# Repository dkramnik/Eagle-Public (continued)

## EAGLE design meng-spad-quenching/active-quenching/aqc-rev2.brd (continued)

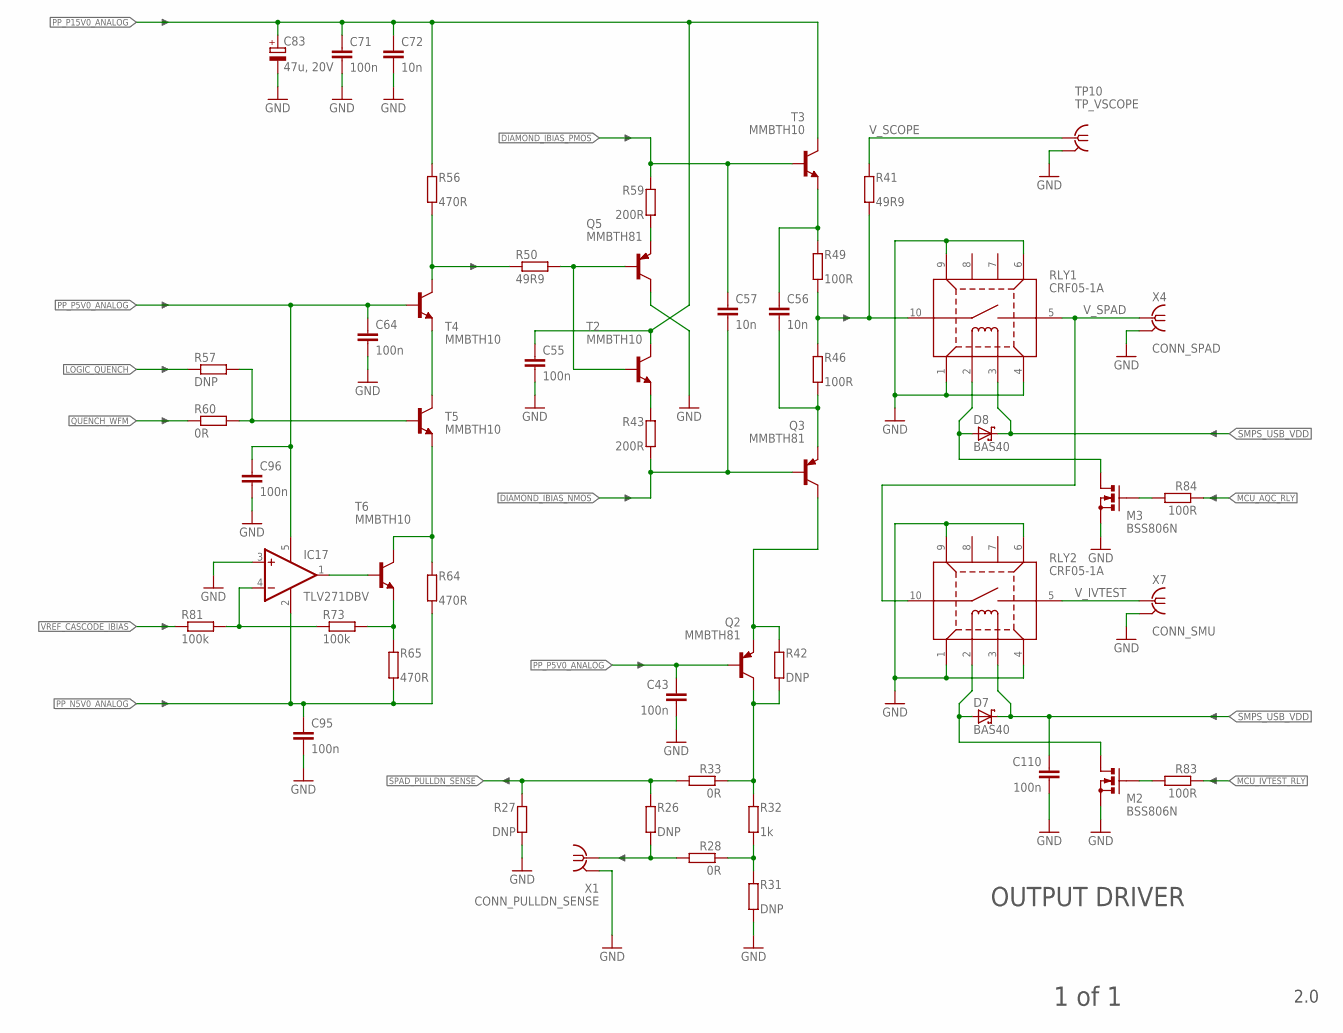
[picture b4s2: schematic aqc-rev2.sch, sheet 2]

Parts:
C43, C55, C64, C71, C95, C96, C110: 100n; C0603
C56, C57, C72: 10n; C0603
C83: 47u, 20V; CT7343
D7, D8: BAS40; SOT23
IC17: TLV271DBV; SOT23-5
M2, M3: BSS806N; SOT23R_INFINEON
Q2, Q3, Q5: MMBTH81; SOT23-BEC
R26, R27, R31, R42, R57: DNP; R0603
R28, R33, R60: 0R; R0603
R32: 1k; R0603
R41, R50: 49R9; R0603
R43, R59: 200R; R0603
R46, R49, R83, R84: 100R; R0603
R56, R64, R65: 470R; R0603
R73, R81: 100k; R0603
RLY1, RLY2: CRF05-1A; MEDER_RELAY_CRF
T2, T3, T4, T5, T6: MMBTH10; SOT23-BEC
TP10: TP_VSCOPE; JOHNSON-129-0701-30X
X1: CONN_PULLDN_SENSE; J502-ND-142-0711-871/876; MPN 142-0711-871
X4: CONN_SPAD; J502-ND-142-0711-871/876
X7: CONN_SMU; J502-ND-142-0711-871/876

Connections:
CASC_BIAS_B: IC17.1 (OUT), T6.B
CASC_BIAS_C: R64.2, T5.E, T6.C
CASC_BIAS_E: R65.2, R73.1, T6.E
CASC_BIAS_VGND: IC17.4 (-IN), R73.2, R81.1
CASC_MIDPT: T4.E, T5.C
DIAMOND_IBIAS_NMOS: C57.2, Q3.B, R43.1; also elsewhere on the board
DIAMOND_IBIAS_PMOS: C57.1, R59.2, T3.B; also elsewhere on the board
GND: C43.2, C55.2, C64.2, C71.2, C72.2, C83.-, C95.2, C96.2, C110.2, IC17.3 (+IN), M2.2 (S), M3.2 (S), Q5.C, R27.1, R31.1, RLY1.1 (PIN1), RLY1.4 (PIN4), RLY1.6 (PIN6), RLY1.9 (PIN9), RLY2.1 (PIN1), RLY2.4 (PIN4), RLY2.6 (PIN6), RLY2.9 (PIN9), TP10.GND1 (GND), TP10.GND2 (GND), X1.G@1 (GND), X1.G@2 (GND), X1.G@3 (GND), X1.G@4 (GND), X4.G@1 (GND), X4.G@2 (GND), X4.G@3 (GND), X4.G@4 (GND), X7.G@1 (GND), X7.G@2 (GND), X7.G@3 (GND), X7.G@4 (GND); also elsewhere on the board
LOGIC_QUENCH: R57.2; also elsewhere on the board
MCU_AQC_RLY: R84.2; also elsewhere on the board
MCU_IVTEST_RLY: R83.2; also elsewhere on the board
unnamed: R57.1, R60.1, T5.B
unnamed: M3.1 (G), R84.1
unnamed: D8.1 (A), M3.3 (D), RLY1.2 (PIN2)
unnamed: C56.1, R49.2, T3.E
unnamed: D7.1 (A), M2.3 (D), RLY2.2 (PIN2)
unnamed: Q2.E, Q3.C, R42.2
unnamed: Q5.E, R59.1
unnamed: R43.2, T2.E
unnamed: C56.2, Q3.E, R46.1
unnamed: M2.1 (G), R83.1
unnamed: Q5.B, R50.1, T2.B
unnamed: R50.2, R56.1, T4.C
unnamed: R41.1, R46.2, R49.1, RLY1.10 (PIN10)
unnamed: Q2.C, R32.2, R33.2, R42.1
unnamed: R28.2, R31.2, R32.1
unnamed: R26.1, R28.1, X1.1
PP_N5V0_ANALOG: C95.1, IC17.2 (V-), R64.1, R65.1; also elsewhere on the board
PP_P5V0_ANALOG: C43.1, C64.1, C96.1, IC17.5 (V+), Q2.B, T4.B; also elsewhere on the board
PP_P15V0_ANALOG: C55.1, C71.1, C72.1, C83.+, R56.2, T2.C, T3.C; also elsewhere on the board
QUENCH_WFM: R60.2; also elsewhere on the board
SMPS_USB_VDD: C110.1, D7.3 (C), D8.3 (C), RLY1.3 (PIN3), RLY2.3 (PIN3); also elsewhere on the board
SPAD_PULLDN_SENSE: R26.2, R27.2, R33.1; also elsewhere on the board
VREF_CASCODE_IBIAS: R81.2; also elsewhere on the board
V_IVTEST: RLY2.5 (PIN5), X7.1
V_SCOPE: R41.2, TP10.SIG (1)
V_SPAD: RLY1.5 (PIN5), RLY2.10 (PIN10), X4.1

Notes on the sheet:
OUTPUT DRIVER
2.0
1 of 1

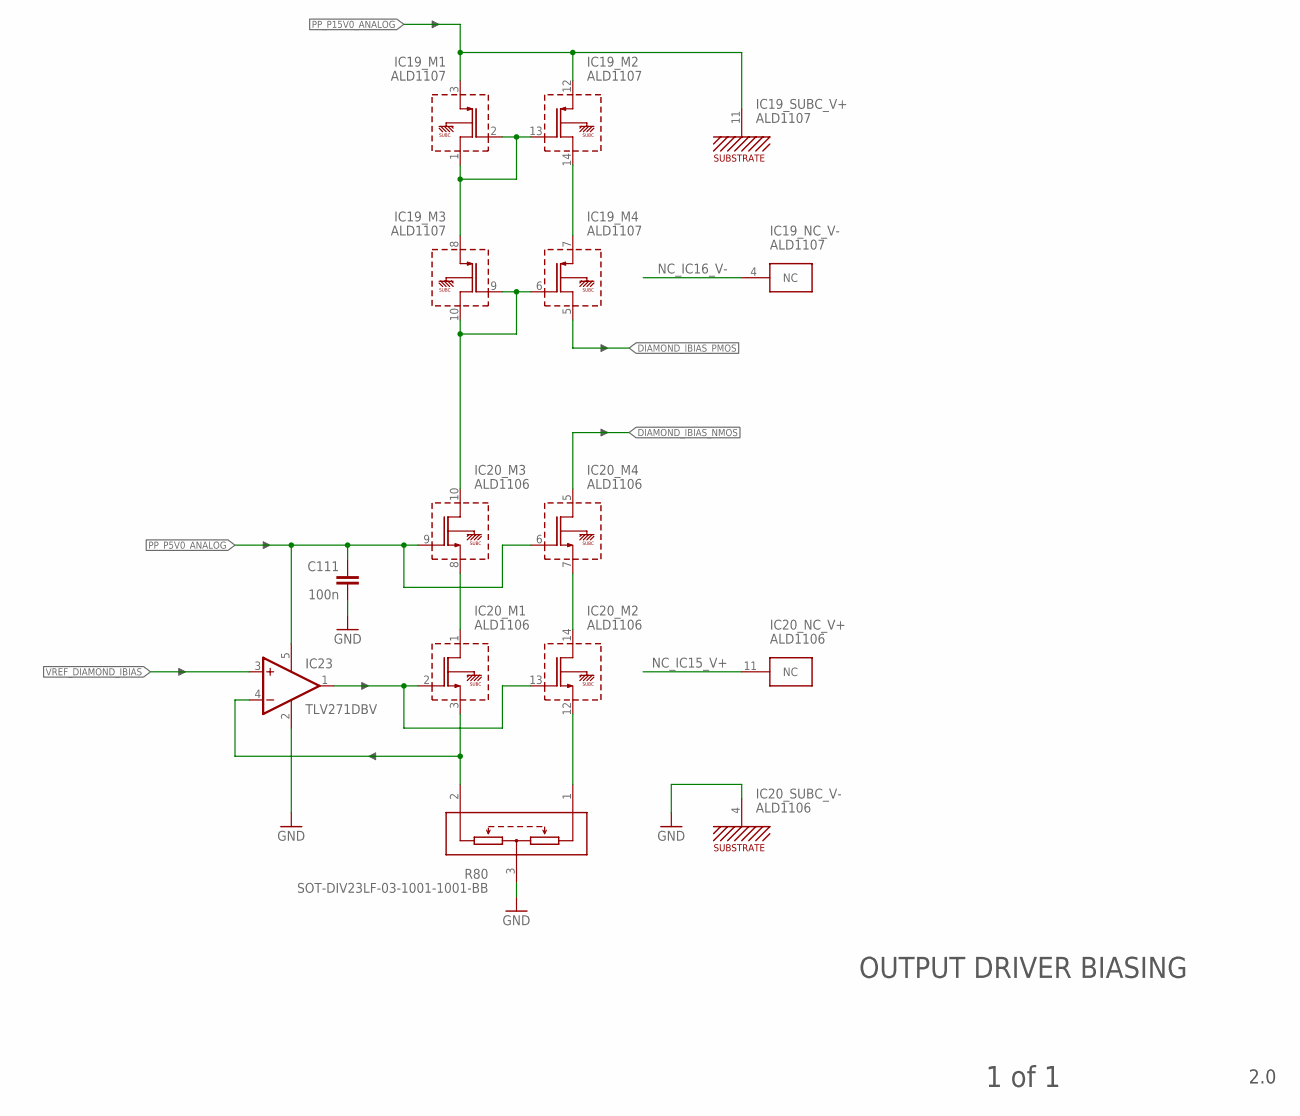
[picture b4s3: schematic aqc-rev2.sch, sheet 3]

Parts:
C111: 100n; C0603
IC19: ALD1107; SO14
IC20: ALD1106; SO14
IC23: TLV271DBV; SOT23-5
R80: SOT-DIV23LF-03-1001-1001-BB; SOT23C

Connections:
DIAMOND_IBIAS_NMOS: IC20.5 (D); also elsewhere on the board
DIAMOND_IBIAS_PMOS: IC19.5 (D); also elsewhere on the board
GND: C111.2, IC20.4 (SUBC), IC23.2 (V-), R80.3 (MIDDLE); also elsewhere on the board
unnamed: IC20.1 (D), IC20.8 (S)
unnamed: IC20.7 (S), IC20.14 (D)
unnamed: IC20.3 (S), IC23.4 (-IN), R80.2 (TOP)
unnamed: IC20.2 (G), IC20.13 (G), IC23.1 (OUT)
unnamed: IC20.12 (S), R80.1 (BOTTOM)
unnamed: IC19.1 (D), IC19.2 (G), IC19.8 (S), IC19.13 (G)
unnamed: IC19.7 (S), IC19.14 (D)
unnamed: IC19.6 (G), IC19.9 (G), IC19.10 (D), IC20.10 (D)
NC_IC15_V+: IC20.11 (NC)
NC_IC16_V-: IC19.4 (NC)
PP_P5V0_ANALOG: C111.1, IC20.6 (G), IC20.9 (G), IC23.5 (V+); also elsewhere on the board
PP_P15V0_ANALOG: IC19.3 (S), IC19.11 (SUBC), IC19.12 (S); also elsewhere on the board
VREF_DIAMOND_IBIAS: IC23.3 (+IN); also elsewhere on the board

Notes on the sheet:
OUTPUT DRIVER BIASING
2.0
1 of 1

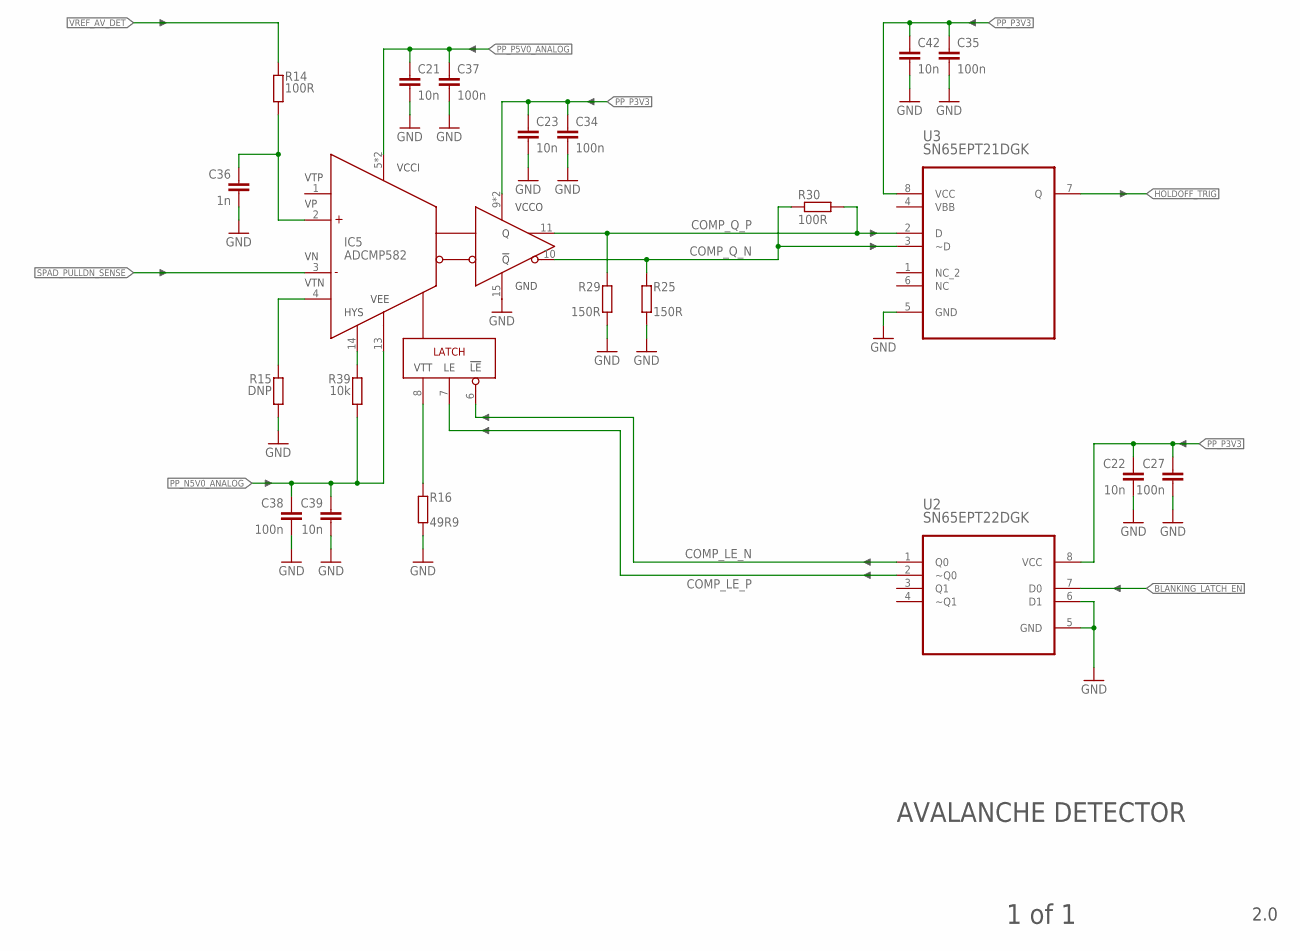
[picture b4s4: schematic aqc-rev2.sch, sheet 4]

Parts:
C21, C22, C23, C39, C42: 10n; C0402
C27, C34, C35, C37, C38: 100n; C0402
C36: 1n; C0603
IC5: ADCMP582; QFN50P300X300X80-16N
R14: 100R; R0603
R15: DNP; R0603
R16: 49R9; R0603
R25, R29: 150R; R0402
R30: 100R; R0402
R39: 10k; R0603
U2: SN65EPT22DGK; SOP65P490X110-8N
U3: SN65EPT21DGK; SOP65P490X110-8N

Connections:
BLANKING_LATCH_EN: U2.7 (D0); also elsewhere on the board
COMP_HYS: IC5.14 (HYS), R39.2
COMP_LE_N: IC5.6 (!LE), U2.1 (Q0)
COMP_LE_P: IC5.7 (LE), U2.2 (~Q0)
COMP_Q_N: IC5.10 (!Q), R25.1, R30.1, U3.3 (~D)
COMP_Q_P: IC5.11 (Q), R29.1, R30.2, U3.2 (D)
COMP_VP: C36.1, IC5.2 (VP), R14.1
COMP_VTN: IC5.4 (VTN), R15.2
COMP_VTT: IC5.8 (VTT), R16.1
GND: C21.2, C22.2, C23.2, C27.2, C34.2, C35.2, C36.2, C37.2, C38.2, C39.2, C42.2, IC5.15 (GND), R15.1, R16.2, R25.2, R29.2, U2.5 (GND), U2.6 (D1), U3.5 (GND); also elsewhere on the board
HOLDOFF_TRIG: U3.7 (Q); also elsewhere on the board
PP_N5V0_ANALOG: C38.1, C39.1, IC5.13 (VEE), R39.1; also elsewhere on the board
PP_P3V3: C22.1, C23.1, C27.1, C34.1, C35.1, C42.1, IC5.9 (VCCO), IC5.12 (VCCO), U2.8 (VCC), U3.8 (VCC); also elsewhere on the board
PP_P5V0_ANALOG: C21.1, C37.1, IC5.5 (VCCI), IC5.16 (VCCI); also elsewhere on the board
SPAD_PULLDN_SENSE: IC5.3 (VN); also elsewhere on the board
VBB: U3.4 (VBB)
VREF_AV_DET: R14.2; also elsewhere on the board

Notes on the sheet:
AVALANCHE DETECTOR
2.0
1 of 1

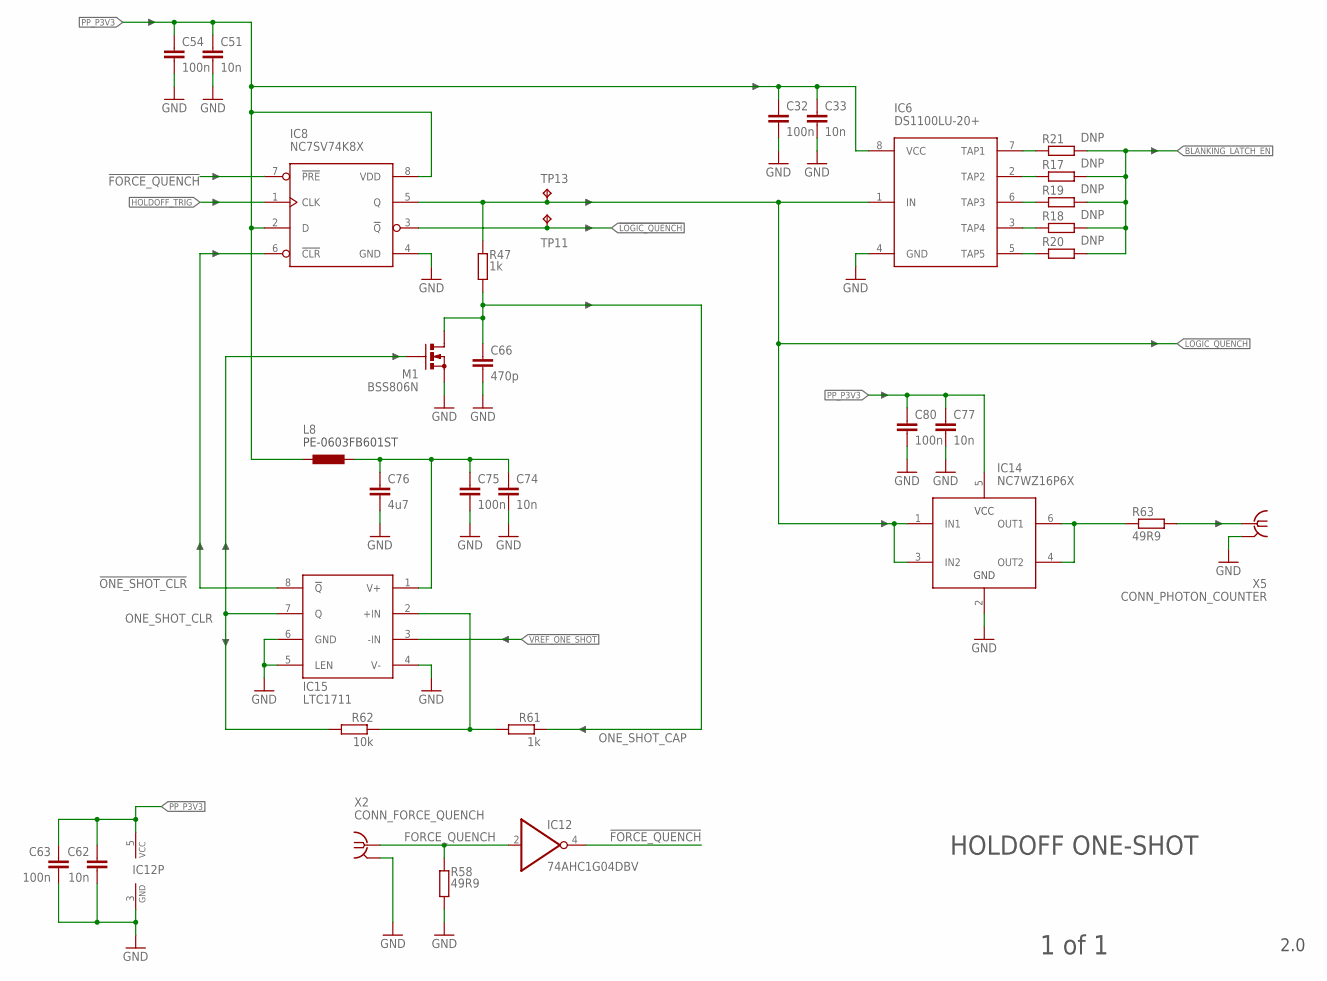
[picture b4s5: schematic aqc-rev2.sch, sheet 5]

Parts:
C32, C54, C63, C75, C80: 100n; C0402
C33, C51, C62, C74, C77: 10n; C0402
C66: 470p; C0603
C76: 4u7; C0603
IC6: DS1100LU-20+; MSOP8
IC8: NC7SV74K8X; US8_3.1MM_JDEC_MO-187
IC12: 74AHC1G04DBV; SOT23-5
IC14: NC7WZ16P6X; SC70-6L
IC15: LTC1711; MSOP8
L8: PE-0603FB601ST; R0603
M1: BSS806N; SOT23R_INFINEON
R17, R18, R19, R20, R21: DNP; R0603
R47, R61: 1k; R0603
R58, R63: 49R9; R0603
R62: 10k; R0603
TP11, TP13: TPTP06R; TP06R
X2: CONN_FORCE_QUENCH; J502-ND-142-0711-871/876; MPN 142-0711-871
X5: CONN_PHOTON_COUNTER; J502-ND-142-0711-871/876

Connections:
!FORCE_QUENCH: IC8.7 (!PRE), IC12.4 (O)
!LOGIC_QUENCH: IC8.3 (!Q), TP11.TP; also elsewhere on the board
!ONE_SHOT_CLR: IC8.6 (!CLR), IC15.8 (!Q)
BLANKING_LATCH_EN: R17.1, R18.1, R19.1, R20.1, R21.1; also elsewhere on the board
FORCE_QUENCH: IC12.2 (I), R58.2, X2.1
GND: C32.2, C33.2, C51.2, C54.2, C62.2, C63.2, C66.2, C74.2, C75.2, C76.2, C77.2, C80.2, IC6.4 (GND), IC8.4 (GND), IC12.3 (GND), IC14.2 (GND), IC15.4 (V-), IC15.5 (LEN), IC15.6 (GND), M1.2 (S), R58.1, X2.G@1 (GND), X2.G@2 (GND), X2.G@3 (GND), X2.G@4 (GND), X5.G@1 (GND), X5.G@2 (GND), X5.G@3 (GND), X5.G@4 (GND); also elsewhere on the board
HOLDOFF_TRIG: IC8.1 (CLK); also elsewhere on the board
LOGIC_QUENCH: IC6.1 (IN), IC8.5 (Q), IC14.1 (IN1), IC14.3 (IN2), R47.2, TP13.TP; also elsewhere on the board
unnamed: IC15.2 (+IN), R61.1, R62.2
unnamed: IC14.4 (OUT2), IC14.6 (OUT1), R63.2
ONE_SHOT_CAP: C66.1, M1.3 (D), R47.1, R61.2
ONE_SHOT_CLR: IC15.7 (Q), M1.1 (G), R62.1
PHOTON_COUNT_OUT: R63.1, X5.1
PP_P3V3: C32.1, C33.1, C51.1, C54.1, C62.1, C63.1, C77.1, C80.1, IC6.8 (VCC), IC8.2 (D), IC8.8 (VDD), IC12.5 (VCC), IC14.5 (VCC), L8.1; also elsewhere on the board
PP_P3V3_COMP: C74.1, C75.1, C76.1, IC15.1 (V+), L8.2
TAP1: IC6.7 (TAP1), R21.2
TAP2: IC6.2 (TAP2), R17.2
TAP3: IC6.6 (TAP3), R19.2
TAP4: IC6.3 (TAP4), R18.2
TAP5: IC6.5 (TAP5), R20.2
VREF_ONE_SHOT: IC15.3 (-IN); also elsewhere on the board

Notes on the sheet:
HOLDOFF ONE-SHOT
2.0
1 of 1

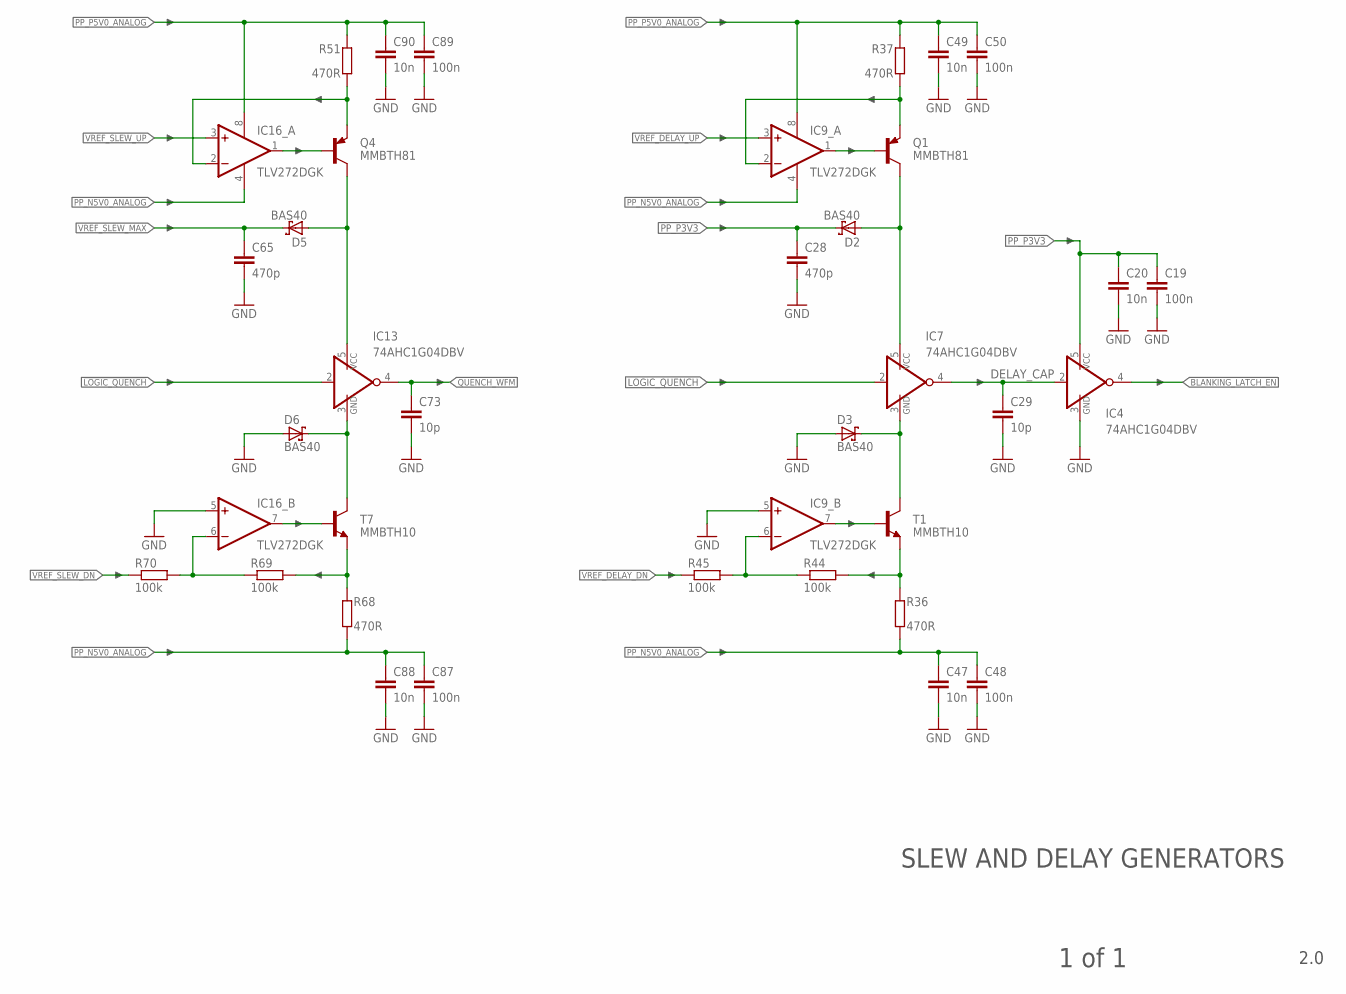
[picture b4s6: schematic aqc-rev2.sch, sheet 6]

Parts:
C19, C48, C50, C87, C89: 100n; C0402
C20, C47, C49, C88, C90: 10n; C0402
C28, C65: 470p; C0603
C29, C73: 10p; C0603
D2, D3, D5, D6: BAS40; SOT23
IC4, IC7, IC13: 74AHC1G04DBV; SOT23-5
IC9, IC16: TLV272DGK; MSOP8
Q1, Q4: MMBTH81; SOT23-BEC
R36, R37, R51, R68: 470R; R0603
R44, R45, R69, R70: 100k; R0603
T1, T7: MMBTH10; SOT23-BEC

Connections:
!LOGIC_QUENCH: IC13.2 (I); also elsewhere on the board
BLANKING_LATCH_EN: IC4.4 (O); also elsewhere on the board
DELAY_CAP: C29.1, IC4.2 (I), IC7.4 (O)
GND: C19.2, C20.2, C28.2, C29.2, C47.2, C48.2, C49.2, C50.2, C65.2, C73.2, C87.2, C88.2, C89.2, C90.2, D3.1 (A), D6.1 (A), IC4.3 (GND), IC9.5 (+IN), IC16.5 (+IN); also elsewhere on the board
LOGIC_QUENCH: IC7.2 (I); also elsewhere on the board
unnamed: IC16.2 (-IN), Q4.E, R51.1
unnamed: D5.1 (A), IC13.5 (VCC), Q4.C
unnamed: D6.3 (C), IC13.3 (GND), T7.C
unnamed: IC16.1 (OUT), Q4.B
unnamed: IC16.7 (OUT), T7.B
unnamed: IC16.6 (-IN), R69.2, R70.1
unnamed: D2.1 (A), IC7.5 (VCC), Q1.C
unnamed: D3.3 (C), IC7.3 (GND), T1.C
unnamed: IC9.7 (OUT), T1.B
unnamed: IC9.6 (-IN), R44.2, R45.1
unnamed: IC9.2 (-IN), Q1.E, R37.1
unnamed: IC9.1 (OUT), Q1.B
unnamed: R68.2, R69.1, T7.E
unnamed: R36.2, R44.1, T1.E
PP_N5V0_ANALOG: C47.1, C48.1, C87.1, C88.1, IC9.4 (V-), IC16.4 (V-), R36.1, R68.1; also elsewhere on the board
PP_P3V3: C19.1, C20.1, C28.1, D2.3 (C), IC4.5 (VCC); also elsewhere on the board
PP_P5V0_ANALOG: C49.1, C50.1, C89.1, C90.1, IC9.8 (V+), IC16.8 (V+), R37.2, R51.2; also elsewhere on the board
QUENCH_WFM: C73.1, IC13.4 (O); also elsewhere on the board
VREF_DELAY_DN: R45.2; also elsewhere on the board
VREF_DELAY_UP: IC9.3 (+IN); also elsewhere on the board
VREF_SLEW_DN: R70.2; also elsewhere on the board
VREF_SLEW_MAX: C65.1, D5.3 (C); also elsewhere on the board
VREF_SLEW_UP: IC16.3 (+IN); also elsewhere on the board

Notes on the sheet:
SLEW AND DELAY GENERATORS
2.0
1 of 1

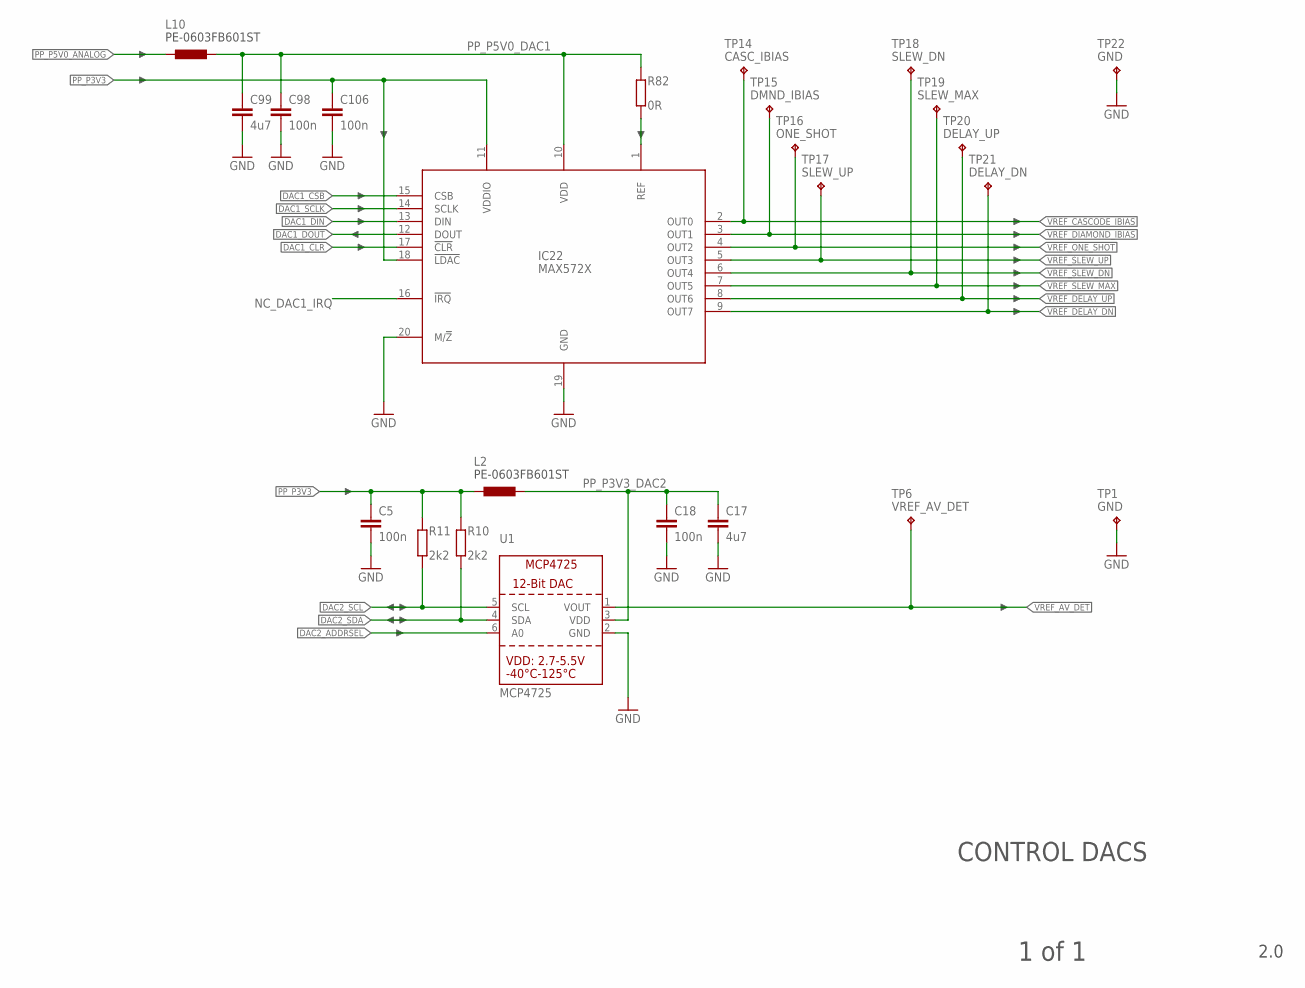
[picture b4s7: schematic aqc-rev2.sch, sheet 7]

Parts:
C5, C18, C98, C106: 100n; C0603
C17, C99: 4u7; C0603
IC22: MAX572X; TSSOP20
L2, L10: PE-0603FB601ST; R0603
R10, R11: 2k2; R0603
R82: 0R; R0603
TP1, TP22: GND; KEYSTONE_5000_MINIATURE
TP6: VREF_AV_DET; KEYSTONE_5000_MINIATURE
TP14: CASC_IBIAS; KEYSTONE_5000_MINIATURE
TP15: DMND_IBIAS; KEYSTONE_5000_MINIATURE
TP16: ONE_SHOT; KEYSTONE_5000_MINIATURE
TP17: SLEW_UP; KEYSTONE_5000_MINIATURE
TP18: SLEW_DN; KEYSTONE_5000_MINIATURE
TP19: SLEW_MAX; KEYSTONE_5000_MINIATURE
TP20: DELAY_UP; KEYSTONE_5000_MINIATURE
TP21: DELAY_DN; KEYSTONE_5000_MINIATURE
U1: MCP4725; SOT23-6

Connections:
DAC1_!CLR: IC22.17 (!CLR); also elsewhere on the board
DAC1_CSB: IC22.15 (CSB); also elsewhere on the board
DAC1_DIN: IC22.13 (DIN); also elsewhere on the board
DAC1_DOUT: IC22.12 (DOUT); also elsewhere on the board
DAC1_SCLK: IC22.14 (SCLK); also elsewhere on the board
DAC2_ADDRSEL: U1.6 (A0); also elsewhere on the board
DAC2_SCL: R11.2, U1.5 (SCL); also elsewhere on the board
DAC2_SDA: R10.2, U1.4 (SDA); also elsewhere on the board
GND: C5.2, C17.2, C18.2, C98.2, C99.2, C106.2, IC22.19 (GND), IC22.20 (M/!Z), TP1.P$1, TP22.P$1, U1.2 (GND); also elsewhere on the board
unnamed: IC22.1 (REF), R82.2
NC_DAC1_IRQ: IC22.16 (!IRQ)
PP_P3V3: C5.1, C106.1, IC22.11 (VDDIO), IC22.18 (!LDAC), L2.1, R10.1, R11.1; also elsewhere on the board
PP_P3V3_DAC2: C17.1, C18.1, L2.2, U1.3 (VDD)
PP_P5V0_ANALOG: L10.1; also elsewhere on the board
PP_P5V0_DAC1: C98.1, C99.1, IC22.10 (VDD), L10.2, R82.1
VREF_AV_DET: TP6.P$1, U1.1 (VOUT); also elsewhere on the board
VREF_CASCODE_IBIAS: IC22.2 (OUT0), TP14.P$1; also elsewhere on the board
VREF_DELAY_DN: IC22.9 (OUT7), TP21.P$1; also elsewhere on the board
VREF_DELAY_UP: IC22.8 (OUT6), TP20.P$1; also elsewhere on the board
VREF_DIAMOND_IBIAS: IC22.3 (OUT1), TP15.P$1; also elsewhere on the board
VREF_ONE_SHOT: IC22.4 (OUT2), TP16.P$1; also elsewhere on the board
VREF_SLEW_DN: IC22.6 (OUT4), TP18.P$1; also elsewhere on the board
VREF_SLEW_MAX: IC22.7 (OUT5), TP19.P$1; also elsewhere on the board
VREF_SLEW_UP: IC22.5 (OUT3), TP17.P$1; also elsewhere on the board

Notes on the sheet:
CONTROL DACS
2.0
1 of 1

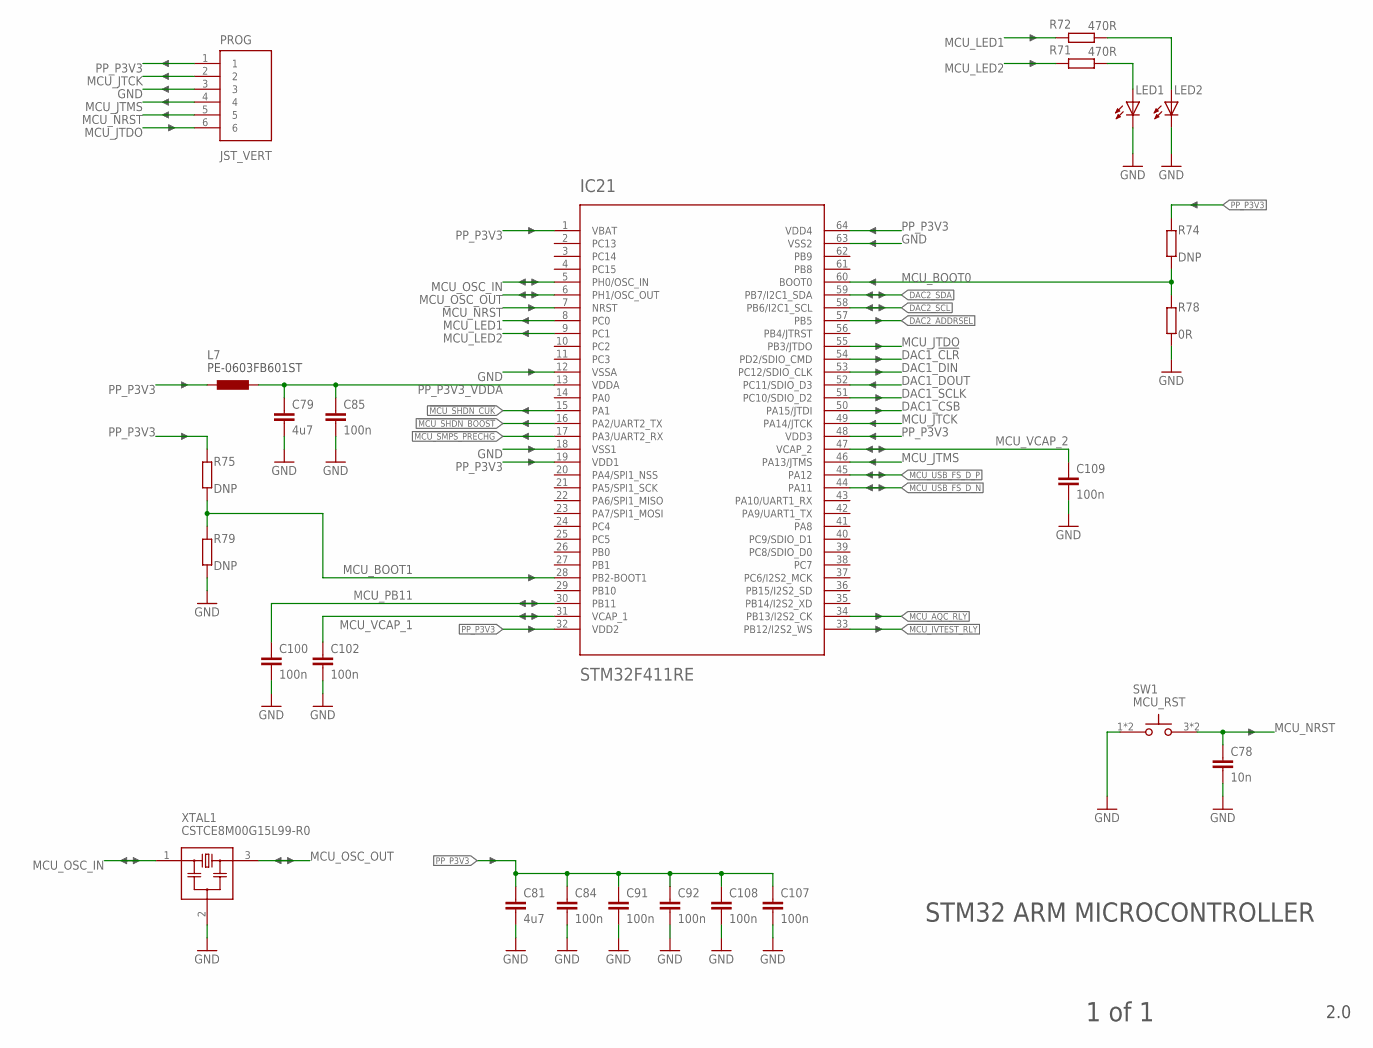
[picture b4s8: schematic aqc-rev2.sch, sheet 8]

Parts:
C78: 10n; C0603
C79, C81: 4u7; C0603
C84, C85, C91, C92, C100, C102, C107, C108, C109: 100n; C0603
IC21: STM32F411RE; TQFP64_STM32
L7: PE-0603FB601ST; R0603
LED1, LED2: LEDCHIP-LED0805; CHIP-LED0805
PROG: JST_VERT; JST-6-SMD-VERT-1.0MM
R71, R72: 470R; R0603
R74, R75, R79: DNP; R0603
R78: 0R; R0603
SW1: MCU_RST; E-SWITCH-TL3305AF160QG
XTAL1: CSTCE8M00G15L99-R0; CSTCE_G15L/CSTCE_GH5L

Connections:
!MCU_SHDN_BOOST: IC21.16 (PA2/UART2_TX); also elsewhere on the board
!MCU_SHDN_CUK: IC21.15 (PA1); also elsewhere on the board
!MCU_SMPS_PRECHG: IC21.17 (PA3/UART2_RX); also elsewhere on the board
DAC1_!CLR: IC21.54 (PD2/SDIO_CMD); also elsewhere on the board
DAC1_CSB: IC21.50 (PA15/JTDI); also elsewhere on the board
DAC1_DIN: IC21.53 (PC12/SDIO_CLK); also elsewhere on the board
DAC1_DOUT: IC21.52 (PC11/SDIO_D3); also elsewhere on the board
DAC1_SCLK: IC21.51 (PC10/SDIO_D2); also elsewhere on the board
DAC2_ADDRSEL: IC21.57 (PB5); also elsewhere on the board
DAC2_SCL: IC21.58 (PB6/I2C1_SCL); also elsewhere on the board
DAC2_SDA: IC21.59 (PB7/I2C1_SDA); also elsewhere on the board
GND: C78.2, C79.2, C81.2, C84.2, C85.2, C91.2, C92.2, C100.2, C102.2, C107.2, C108.2, C109.2, IC21.12 (VSSA), IC21.18 (VSS1), IC21.63 (VSS2), LED1.C, LED2.C, PROG.3, R78.2, R79.2, SW1.1, SW1.2, XTAL1.2 (GND); also elsewhere on the board
MCU_AQC_RLY: IC21.34 (PB13/I2S2_CK); also elsewhere on the board
MCU_BOOT0: IC21.60 (BOOT0), R74.2, R78.1
MCU_BOOT1: IC21.28 (PB2-BOOT1), R75.2, R79.1
MCU_IVTEST_RLY: IC21.33 (PB12/I2S2_WS); also elsewhere on the board
MCU_JTCK: IC21.49 (PA14/JTCK), PROG.2
MCU_JTDO: IC21.55 (PB3/JTDO), PROG.6
MCU_JTMS: IC21.46 (PA13/JTMS), PROG.4
MCU_LED1: IC21.8 (PC0), R72.2
MCU_LED2: IC21.9 (PC1), R71.2
MCU_NRST: C78.1, IC21.7 (NRST), PROG.5, SW1.3, SW1.4
MCU_OSC_IN: IC21.5 (PH0/OSC_IN), XTAL1.1 (LEFT)
MCU_OSC_OUT: IC21.6 (PH1/OSC_OUT), XTAL1.3 (RIGHT)
MCU_PB11: C100.1, IC21.30 (PB11)
MCU_USB_FS_D_N: IC21.44 (PA11); also elsewhere on the board
MCU_USB_FS_D_P: IC21.45 (PA12); also elsewhere on the board
MCU_VCAP_1: C102.1, IC21.31 (VCAP_1)
MCU_VCAP_2: C109.1, IC21.47 (VCAP_2)
unnamed: LED2.A, R72.1
unnamed: LED1.A, R71.1
PP_P3V3: C81.1, C84.1, C91.1, C92.1, C107.1, C108.1, IC21.1 (VBAT), IC21.19 (VDD1), IC21.32 (VDD2), IC21.48 (VDD3), IC21.64 (VDD4), L7.1, PROG.1, R74.1, R75.1; also elsewhere on the board
PP_P3V3_VDDA: C79.1, C85.1, IC21.13 (VDDA), L7.2

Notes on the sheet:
STM32 ARM MICROCONTROLLER
2.0
1 of 1

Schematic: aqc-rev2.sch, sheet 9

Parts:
C31: 47u, 20V; CT7343
C82, C103, C104: 100n; C0603
C86: 100n; C0402
C93: 10n; C0402
C94, C97: 47p; C0402
C101: 10n; C0603
C105: 4u7; C0603
H1, H2, H3, H4: MOUNT-PAD-ROUND3.2; 3,2-PAD
IC18: USBLC6-2SC6Y; SOT23-6L
IC24: LM1117; SOT-223
L9, L11: MI0805J102R-10; R0805
Q6: IRLML6402TRPBF; SOT23-WIDE
R66: 4k7; R0603
R67: 100k; R0603
R76, R77: 22R; R0402
TP23: TPTP15R; TP15R
X3, X6: KEYSTONE-7774
X8: PN61729-S

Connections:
!MCU_SMPS_PRECHG: R66.2; also elsewhere on the board
GND: C31.-, C86.2, C93.2, C94.2, C97.2, C101.2, C103.2, C104.2, C105.2, H1.B3,2, H2.B3,2, H3.B3,2, H4.B3,2, IC18.2 (GND), IC24.1 (GND), L11.2, X3.1, X3.2, X3.3, X3.4, X6.1, X6.2, X6.3, X6.4, X8.S1, X8.S2; also elsewhere on the board
MCU_USB_FS_D_N: C97.1, R77.1; also elsewhere on the board
MCU_USB_FS_D_P: C94.1, R76.1; also elsewhere on the board
unnamed: C82.1, Q6.1 (G), R66.1, R67.1
PP_P3V3: C86.1, C93.1, C103.1, IC18.5 (VBUS), IC24.2 (OUT), IC24.4 (TAB), TP23.TP; also elsewhere on the board
SMPS_USB_VDD: C31.+, C82.2, Q6.3 (D); also elsewhere on the board
USBCONN_P1: C101.1, L9.1, X8.1
USBCONN_P4: L11.1, X8.4
USBD_CONN_N: IC18.3 (I/O2), X8.2
USBD_CONN_P: IC18.1 (I/O1_1), X8.3
USBD_TVS_N: IC18.4 (I/O2_2), R77.2
USBD_TVS_P: IC18.6 (I/O1_2), R76.2
USB_VDD: C104.1, C105.1, IC24.3 (IN), L9.2, Q6.2 (S), R67.2

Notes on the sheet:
USB INPUT AND INRUSH LIMITING
2.0
1 of 1

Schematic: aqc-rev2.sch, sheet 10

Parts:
C3: 1n; C0603
C4: 1300p; C0603
C14, C15, C30: 47u, 20V; CT7343
C16: 4u7; C0805
C24: 100n; C0603
C25: 15n; C0603
C26: 220p; C0603
D1: CDBA140SL-HF; DO214AC
IC3: LT1534-1; SO16
L1: 25n; R0603
L3, L4: SRF0703-820M; SRF0703
R3, R5: DNP; R0603
R4: 0R; R0603
R6: 29k4; R0603
R7: 2k49; R0603
R8: 10R; R0603
R9: 16k9; R0603
R22, R23: 1k; R0603
R24: 6k8; R0603
TP3, TP7: TPB1,27; B1,27

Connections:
!MCU_SHDN_BOOST: IC3.12 (!SHDN); also elsewhere on the board
BOOST_STAGE1: C14.+, C15.+, D1.C, L3.1, R3.1, R5.1
BOOST_SW_NODE: D1.A, IC3.2 (COL), L4.4, R8.1
GND: C3.1, C4.2, C14.-, C15.-, C16.2, C24.2, C25.2, C26.2, C30.-, IC3.1 (GND), IC3.8 (GND), IC3.9 (GND), IC3.16 (GND), L1.2, R7.2, R9.1, R22.2, R23.2; also elsewhere on the board
LBOOST_2: L3.2, L3.3
LBOOST_!: L4.2, L4.3
unnamed: IC3.7 (FB), R6.1, R7.1
unnamed: IC3.3 (PGND), L1.1
unnamed: C4.1, IC3.5 (CT)
unnamed: IC3.13 (RCSL), R23.1
unnamed: IC3.14 (RVSL), R22.1
unnamed: C3.2, R8.2
unnamed: C25.1, R24.1
unnamed: C26.1, IC3.11 (VC), R24.2
unnamed: IC3.6 (RT), R9.2
unnamed: R4.2, R5.2, R6.2
PP_P16V0_BOOST: C30.+, L3.4, R3.2, R4.1; also elsewhere on the board
SMPS_USB_VDD: C16.1, C24.1, IC3.15 (VIN), L4.1; also elsewhere on the board
TP_NFB_BOOST: IC3.10 (NFB), TP7.TP
TP_SYNC_BOOST: IC3.4 (SYNC), TP3.TP

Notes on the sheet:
POSITIVE DC/DC SMPS
2.0
1 of 1

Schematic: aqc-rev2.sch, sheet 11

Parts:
C40: 10n; C0603
C41: 1300p; C0603
C46: 68u, 16V; CT7343
C53, C61: 4u7; C0805
C60: 10u, 10V; C0805
C67: 100n; C0603
C68: 33n; C0603
C69, C70: DNP; C0603
D4: CDBA140SL-HF; DO214AC
IC11: LT1534-1; SO16
L5: 25n; R0603
L6: SRF0703-820M; SRF0703
R34: 100R; R0603
R35: 16k9; R0603
R48: 1k4; R0603
R52, R53, R55: 1k; R0603
R54: 2k; R0603
TP9, TP12: TPB1,27; B1,27

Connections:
!MCU_SHDN_CUK: IC11.12 (!SHDN); also elsewhere on the board
GND: C40.2, C41.2, C53.2, C60.2, C61.2, C67.2, C68.2, C69.2, C70.2, D4.C, IC11.1 (GND), IC11.8 (GND), IC11.9 (GND), IC11.16 (GND), L5.2, R35.1, R52.2, R53.2, R55.2; also elsewhere on the board
unnamed: C41.1, IC11.5 (CT)
unnamed: IC11.3 (PGND), L5.1
unnamed: IC11.13 (RCSL), R53.1
unnamed: IC11.14 (RVSL), R52.1
unnamed: C40.1, R34.2
unnamed: C68.1, R54.1
unnamed: C69.1, IC11.11 (VC), R54.2
unnamed: IC11.6 (RT), R35.2
unnamed: IC11.10 (NFB), R48.2, R55.1
unnamed: C46.+, IC11.2 (COL), L6.3, R34.1
unnamed: C46.-, C70.1, D4.A, L6.4
PP_N6V0_CUK: C60.1, L6.2, R48.1; also elsewhere on the board
SMPS_USB_VDD: C53.1, C61.1, C67.1, IC11.15 (VIN), L6.1; also elsewhere on the board
TP_FB_CUK: IC11.7 (FB), TP12.TP
TP_SYNC_CUK: IC11.4 (SYNC), TP9.TP

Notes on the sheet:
NEGATIVE DC/DC SMPS
2.0
1 of 1

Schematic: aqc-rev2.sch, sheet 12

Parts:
C1, C2, C6, C7, C45, C59: 10n; C0603
C8, C9, C10, C11, C52, C58: 100n; C0603
C12, C13, C44: 10u; C0805
IC1, IC2: TPS7A4901; MSOP-8_POWER_PAD
IC10: TPS7A3001; MSOP-8_POWER_PAD
R1, R40: 24k; R0603
R2: 11k8; R0603
R12, R38: 76k8; R0603
R13: 137k; R0603
TP2, TP4, TP5, TP8: TPTP15R; TP15R

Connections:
GND: C1.2, C2.2, C8.2, C9.2, C10.2, C11.2, C12.2, C13.2, C44.2, C52.2, C58.2, C59.2, IC1.4 (GND), IC1.PAD (GND), IC2.4 (GND), IC2.PAD (GND), IC10.4 (GND), IC10.PAD (GND), R1.2, R2.2, R40.2, TP5.TP; also elsewhere on the board
LDO_N10V0_FB_CH1: C45.2, IC10.2 (FB), R38.1, R40.1
LDO_N10V0_NR_SS_CH1: C59.1, IC10.6 (NR/SS)
LDO_P5V0_FB_CH1: C6.2, IC1.2 (FB), R1.1, R12.1
LDO_P5V0_NR_SS_CH1: C1.1, IC1.6 (NR/SS)
LDO_P10V0_FB_CH1: C7.2, IC2.2 (FB), R2.1, R13.1
LDO_P10V0_NR_SS_CH1: C2.1, IC2.6 (NR/SS)
PP_N5V0_ANALOG: C44.1, C45.1, C52.1, IC10.1 (OUT), R38.2, TP8.TP; also elsewhere on the board
PP_N6V0_CUK: C58.1, IC10.5 (EN), IC10.8 (IN); also elsewhere on the board
PP_P5V0_ANALOG: C6.1, C8.1, C12.1, IC1.1 (OUT), R12.2, TP4.TP; also elsewhere on the board
PP_P15V0_ANALOG: C7.1, C9.1, C10.1, C13.1, IC1.5 (EN), IC1.8 (IN), IC2.1 (OUT), R13.2, TP2.TP; also elsewhere on the board
PP_P16V0_BOOST: C11.1, IC2.5 (EN), IC2.8 (IN); also elsewhere on the board

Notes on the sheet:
LINEAR POSTREGULATORS
2.0
1 of 1
